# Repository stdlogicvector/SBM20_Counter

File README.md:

# SBM20 Counter

With this PCB and an SBM20 tube you can build a small, battery operated geiger counter. It can be supplied by two AA batteries, for example. Depending on the battery type you can populate the Step-Up (<5V) or the Step-Down (>5V).
The left part of the PCB generates the approx. 400V for the tube, the right part amplifies and shapes the pulses for the LED and buzzer.
The buzzer is optional if the LED is sufficient feedback.

## Acknowledgements
The circuit is bodged together from multiple sources on the internet, mainly from [MightyOhm](https://mightyohm.com/files/geiger/geiger_sch_fixedR5R6.png).

## Contact
Send Questions to @stdlogicvector@chaos.social 

## BOM

| **Qty** | **Value** | **Footprint**     | **Parts**         | **DIGIKEY**                 | **LCSC** |
| ------- | --------- | ----------------- | ----------------- | --------------------------- | -------- |
| 1       | Red       | CHIPLED_1206      | LED               |                             |          |
| 1       | 100R      | R-TRIMM3224J      | R14               |                             |          |
| 1       | 1M        | R-EU_R1206        | R2                |                             |          |
| 2       | 1N4148    | SOD123            | D2, D3            |                             |          |
| 2       | 1k        | R-EU_R0603        | R13, R32          |                             |          |
| 1       | 1k5       | R-EU_R0603        | R1                |                             |          |
| 2       | 1n        | C-EUC0603         | C3, C6            |                             |          |
| 1       | 1u        | C-EUC1206         | C9                |                             |          |
| 1       | 2u2       | C-EUC1206         | C10A              |                             |          |
| 1       | 4M7       | R-EU_R1206        | R10               |                             |          |
| 1       | 4k7       | R-EU_R0603        | R9                |                             |          |
| 1       | 10mH      | L-EUL8065         | L1                |                             |          |
| 2       | 10n 630V  | C-EUC1206         | C1, C5            |                             |          |
| 4       | 10u       | C-EUC1206         | C8, C8A, C8B, C10 |                             |          |
| 1       | 20p       | C-EUC0603         | C11               |                             |          |
| 1       | 22R       | R-EU_R0603        | R5                |                             |          |
| 1       | 27k       | R-EU_R0603        | R4                |                             |          |
| 1       | 30R       | R-EU_R0603        | R5A               |                             |          |
| 3       | 100k      | R-EU_R0603        | R7, R11, R12      |                             |          |
| 2       | 100n      | C-EUC0603         | C2, C7            |                             |          |
| 1       | 120k      | R-EU_R0603        | R16               |                             |          |
| 1       | 180k      | R-EU_R0603        | R6                |                             |          |
| 1       | 220k      | R-EU_R0603        | R3                |                             |          |
| 1       | 220p      | C-EUC0603         | C4                |                             |          |
| 1       | 330R      | R-EU_R0603        | R8                |                             |          |
| 1       | 680k      | R-EU_R0603        | R15               |                             |          |
| 1       | CMMR1U-06 | DO-214AC          | D1                | 1514-CMMR1U-06TRPBFREECT-ND |
| 1       | DN350T05  | SOT23             | T1                | DN350T05DICT-ND             |
| 1       | LM555D    | LM555D            | IC2               | LM555CMX/NOPBCT-ND          |
| 1       | LM556D    | LM556D            | IC1               | 2156-LM556CM-FS-ND          |
| 2       | MMBT3904  | SOT23             | T2, T3            | 4530-MMBT3904CT-ND          |
| 2       | SBM20     | FUSECLIP          | SBM20             | F3781-ND                    |          |
| 1       | XC914X    | SOT23-5           | IC3               | 893-1373-1-ND               |          |
| 1       | XC926X    | SOT23-5           | IC3A              | 893-1330-1-ND               |          |
| 2       | 4u7       | L5050             | L2, L2A           | 490-7779-1-ND               |          |
| 1       | KJL-5020  | BUZZER-5020       | BEEP              |                             | C556937  |
| 1       | AO3404A   | SOT23             | T6                |                             | C30010   |
| 1       |           | SWITCH-SPDT-SMD-A | PWR               |                             | C319019  |

The SMB20 tube is available from several ebay sellers.

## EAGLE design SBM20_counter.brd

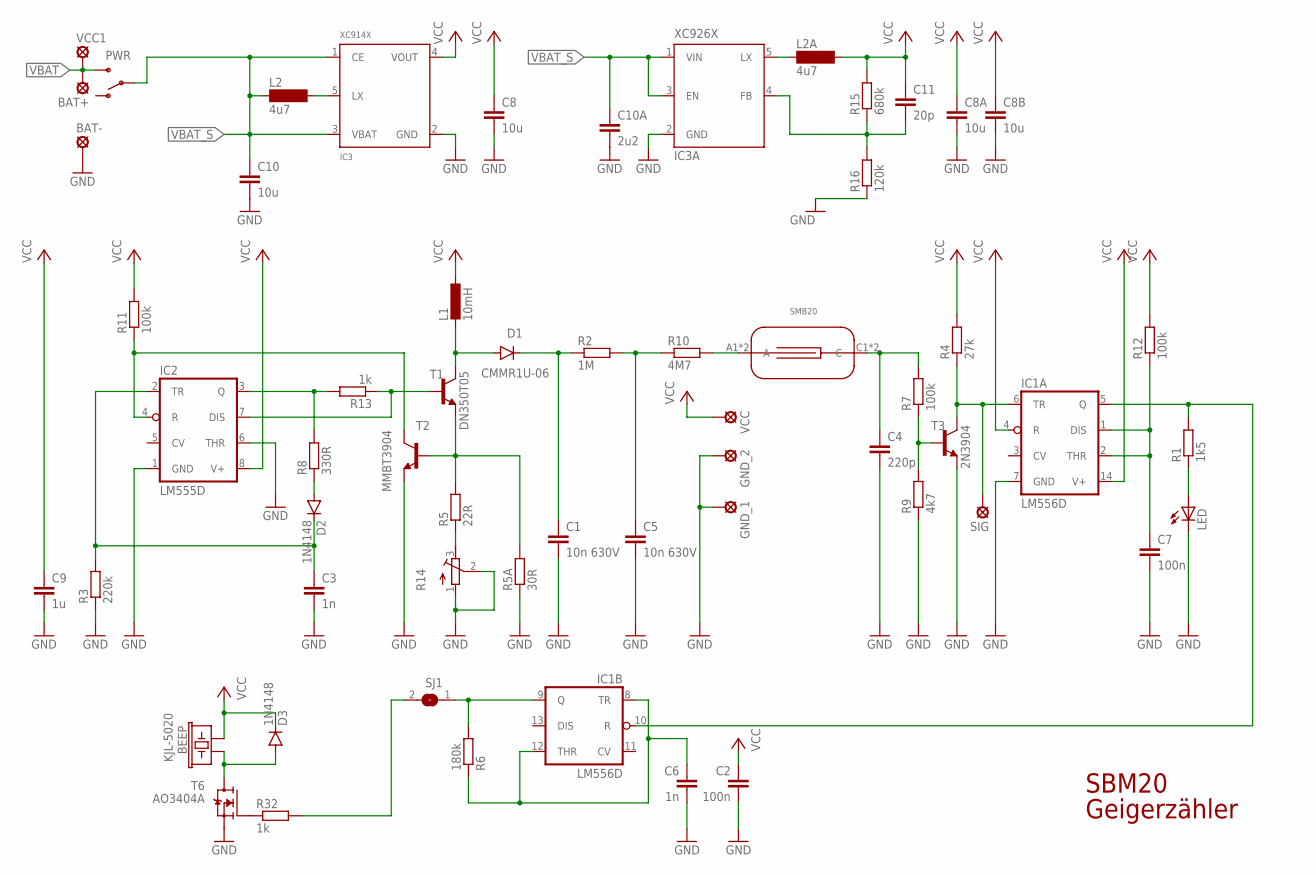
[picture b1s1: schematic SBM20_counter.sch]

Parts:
BAT+: LSP10_CAST; CASTEL_1
BAT-: LSP10_CAST; CASTEL_1
BEEP: KJL-5020; KLJ-5020; LCSC C556937
C1, C5: 10n 630V; C1206
C2, C7: 100n; C0603
C3, C6: 1n; C0603
C4: 220p; C0603
C8, C8A, C8B, C10: 10u; C1206
C9: 1u; C1206
C10A: 2u2; C1206
C11: 20p; C0603
D1: CMMR1U-06; DO-214AC
D2, D3: 1N4148; SOD123
GND_1, GND_2: LSP10_CAST; CASTEL_1
IC1: LM556D; SO14
IC2: LM555D; SO08
IC3: XC914X; SOT23-5; DIGIKEY 893-1373-1-ND
IC3A: XC926X; SOT23-5; DIGIKEY 893-1330-1-ND
L1: 10mH; L8065
L2, L2A: 4u7; L5050; DIGIKEY 490-7779-1-ND
LED: LEDCHIPLED_1206; CHIPLED_1206
PWR: SWITCH-SPDT-SMD-A; SWITCH-SPST-SMD-A; LCSC C319019
R1: 1k5; R0603
R2: 1M; R1206
R3: 220k; R0603
R4: 27k; R0603
R5: 22R; R0603
R5A: 30R; R0603
R6: 180k; R0603
R7, R11, R12: 100k; R0603
R8: 330R; R0603
R9: 4k7; R0603
R10: 4M7; R1206
R13: 1k; R0603
R14: R-TRIMM3224J; RTRIM3224J
R15: 680k; R0603
R16: 120k; R0603
R32: 1k; R0603; LCSC C11702
SIG: LSP10_CAST; CASTEL_1
SJ1: SJ
T1: DN350T05; SOT23-BEC
T2: MMBT3904; SOT23-BEC
T3: 2N3904; SOT23-BEC
T6: AO3404A; SOT23; LCSC C30010
U$1: SMB20; STS5
VCC, VCC1: LSP10_CAST; CASTEL_1

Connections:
GND: BAT-.C, BAT-.V, C1.2, C2.2, C3.2, C4.2, C5.2, C6.2, C7.2, C8.2, C8A.2, C8B.2, C9.2, C10.2, C10A.2, GND_1.C, GND_1.V, GND_2.C, GND_2.V, IC1.7 (GND), IC2.1 (GND), IC2.6 (THR), IC3.2 (GND), IC3A.2 (GND), LED.C, R3.1, R5A.1, R9.1, R14.1 (A), R14.2 (S), R16.1, T2.E, T3.E, T6.2 (S)
unnamed: R5.2, R5A.2, T1.E, T2.B
unnamed: IC2.3 (Q), R8.2, R13.2
unnamed: C3.1, D2.C, IC2.2 (TR), R3.2
unnamed: IC2.4 (R), R11.1, T2.C
unnamed: IC2.7 (DIS), R13.1, T1.B
unnamed: D2.A, R8.1
unnamed: R5.1, R14.3 (E)
unnamed: D1.A, L1.2, T1.C
unnamed: C1.1, D1.C, R2.1
unnamed: C5.1, R2.2, R10.1
unnamed: R10.2, U$1.A1 (A), U$1.A2 (A)
unnamed: C4.1, R7.2, U$1.C1 (C), U$1.C2 (C)
unnamed: R7.1, R9.2, T3.B
unnamed: IC1.6 (TR), R4.1, SIG.C, SIG.V, T3.C
unnamed: IC1.5 (Q), IC1.10 (R), R1.2
unnamed: C7.1, IC1.1 (DIS), IC1.2 (THR), R12.1
unnamed: IC1.9 (Q), R6.2, SJ1.1
unnamed: LED.A, R1.1
unnamed: R32.2, SJ1.2
unnamed: IC3A.5 (LX), L2A.1
unnamed: C6.1, IC1.8 (TR), IC1.12 (THR), R6.1
unnamed: IC3.5 (LX), L2.2
unnamed: C11.2, IC3A.4 (FB), R15.1, R16.2
unnamed: R32.1, T6.1 (G)
unnamed: BEEP.- (2), D3.A, T6.3 (D)
VBAT: BAT+.C, BAT+.V, PWR.3 (S), VCC1.C, VCC1.V
VBAT_S: C10.1, C10A.1, IC3.1 (CE), IC3.3 (VBAT), IC3A.1 (VIN), IC3A.3 (EN), L2.1, PWR.2
VCC: BEEP.+ (1), C2.1, C8.1, C8A.1, C8B.1, C9.1, C11.1, D3.C, IC1.4 (R), IC1.14 (V+), IC2.8 (V+), IC3.4 (VOUT), L1.1, L2A.2, R4.2, R11.2, R12.2, R15.2, VCC.C, VCC.V

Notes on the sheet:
SBM20
Geigerzähler

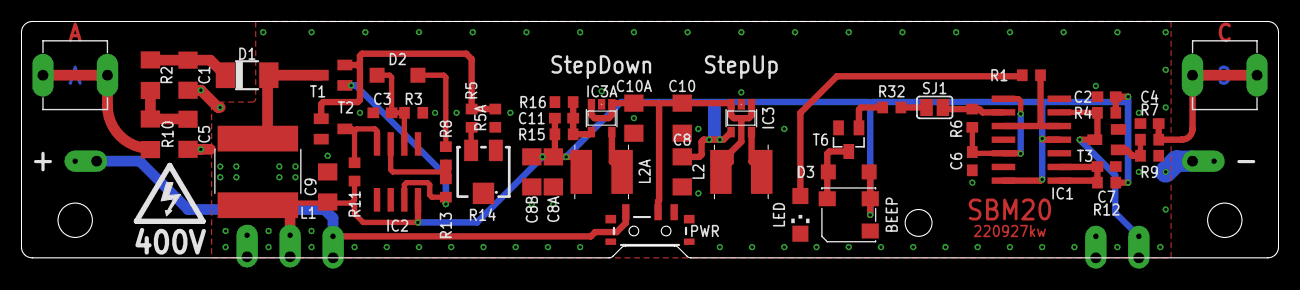
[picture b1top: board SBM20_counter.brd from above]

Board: 2 copper layers, 117.0 x 22.0 mm, 59 parts (0 on the bottom side), 29 nets.

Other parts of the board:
U$2: HIGHVOLTAGE

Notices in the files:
parts and their libraries:
SparkFun-Electromechanical: Licensing: Creative Commons ShareAlike 4.0 International - https://creativecommons.org/licenses/by-sa/4.0
